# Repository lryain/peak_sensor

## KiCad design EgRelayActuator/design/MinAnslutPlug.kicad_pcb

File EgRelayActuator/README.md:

**CAUTION: This project deals with hazardous voltage with the risk of death or personal injury! Please don't do anything unless you are absolutely sure of what you are doing. There is no one liable for the correctness or usage of any information below.**

**Work In Progress**

Discussion, work and various projects have been done or are still going on regarding powering our MySensor/Arduino projects from mains supply. So I think the interest in these projects are pretty high. For this reason I decided to share this project as "work in progress" even though I prefer more completeness before publishing. The prototype PCB needs a couple of minor modifications to work. I only share Kicad design files without Gerbers to make sure anyone doesn't order it without being aware of the necessary mods.

**The Project Concept**

Yet another outlet switch? Well, yes, maybe. Hopefully you'll think I've added some value to it...

I think everyone have seen the cheap remote controlled wireless power outlet switches (here in Sweden usually at 433MHz). They're found in every store. Some are very simple with just a remote control and unknown protocol. Some are rather compatible and then makes quite good as e.g. entry level HA system or part of system. I think most DIY HA system controllers also have the ability to control those protocols and there's also sniffers, bridges and whatever necessary. Here are some threads I found just by a quick search here at the forum:

[http://forum.mysensors.org/topic/2286/experimenting-with-cheap-433mhz-gadgets](http://forum.mysensors.org/topic/2286/experimenting-with-cheap-433mhz-gadgets)

[http://forum.mysensors.org/topic/1621/mysensors-and-433-mhz](http://forum.mysensors.org/topic/1621/mysensors-and-433-mhz)

[http://forum.mysensors.org/topic/1543/universal-gateway-for-315-433mhz-devices](http://forum.mysensors.org/topic/1543/universal-gateway-for-315-433mhz-devices)

[http://forum.mysensors.org/topic/944/one-way-on-how-to-reuse-433mhz-alarming-sensors-for-mysensors](http://forum.mysensors.org/topic/944/one-way-on-how-to-reuse-433mhz-alarming-sensors-for-mysensors)

[http://forum.mysensors.org/topic/1557/combined-mysensor-gateway-with-433mhz-transmitter-homeeasy-klik-aan-klik-uit](http://forum.mysensors.org/topic/1557/combined-mysensor-gateway-with-433mhz-transmitter-homeeasy-klik-aan-klik-uit)
.

What I dislike most about these simple wireless switches are: (1) No duplx (ack) ability. (2) Unreliable reception. (3) They could interfere with each other if too close. (4) No Atmega328p - no playing.
(The more I think about it, the more important is the last (4).)

What I do like most: (1) Cheap (2) Good range. (3) Low power. (4). Small size. 

My first idea was to reuse as much as possible and MySensorize one of these common commercial wall-plugs. I did a few tries reusing some parts of the hardware (PCB and power supply) and squeeze in an Arduino Pro Mini and nRF24L01. I failed. The available power wasn't enough because of the relay and when I upgraded the transformerless supply it became to big to fit in the original enclosure. Thus, I looked for a switching transformer supply instead.

Transformerless supplies are great for low power [class II](http://www.ee-techs.com/test/en60335-1.pdf) devices like this since they're completely insulated. A transformer (-based switch mode-) supply is better for class III devices where the secondary voltage is touchable. But, in this case I had to go for transformer supply because of the space. I can see disadvantages with this choice; (1) Safety - It's much more complex and when ordering from China I'd prefer to trust a single X-cap rather than a whole power supply assembly. (2) Cost - (Not really, because it isn't as great difference as it used to be. Especially considering the work effort with more components of you build a transformerless supply from scratch.). 

To make it easy to design and useful for other future projects as well, I looked for a smaller switched mode power supply (SMPS) than [the famous HLK-PM01](http://lygte-info.dk/review/Power%20Mains%20to%205V%200.6A%20Hi-Link%20HLK-PM01%20UK.html) and then I had to do my own little review of it in [this thread.](http://forum.mysensors.org/topic/3428/my-look-at-a-cheap-12v-power-supply).

**The Enclosure and Original Product**

I went to a local shop and bought the cheapest 3-pack I could find, six months ago. I can't find it at that price (99SEK) any more, but the enclosure is (the most?) common, used by different brands and I guess very available in general. In worst case my new hardware of this project could be redesigned to fit other enclosures.

The internal parts of the original product is like every other of these: Xcap-rectifier-filter, relay, tiny uC with eeprom, radio circuit, etc. Note all the unused space inside the enclosure. Yum yum.

Since I don't have the right triangular shaped tool to release the two screws holding the case halves together, I replaced them as soon as I released them (with a normal flat headed screwdriver of the right size). I found that the screws included in the [10pcs Magnetic Door Switch Sensors](http://www.mysensors.org/store/#locks) make a perfect replacement for these.

**The New Hardware**

Here's my initial requirements. It's important to know that the objective of this first design was to (1) Be safe and (2) Collect info enough to assess reliability. It was not intended to be a final version.

- Standard 5x20mm glass fuse. Proven, high breaking capacity, replaceable and flexible (e.g. testing different values). 
- Thermal fuse(s). Protecting from supply and/or relay overheating consequences.
- Ability to measure temperatures of liable internal overheaters individually.
- Creepage distances with safety margin and a general HV-LV as well as HP-LP separation.
- Heat resistant assembly with robust withstanding insulation between HV conductive parts.
- Standard relay, minimum 10A rated.
- Low high-power resistance.
- EMC (hard to test though)
- Basic MySensors and Arduino functionality, FTDI, ISP
- No new enclosure penetrations (keep it class II)  

Running my Kicad, I came up with this:

Populated it looks like this:

and with lid on it looks like this. As can be seen, instead of one button and one LED, I've put three LEDs.

Features of this prototype fulfil my overall requirements listed above (...I think. I really need a second opinion though.) To be more specific:

- Robust assembly where the supply module is attached to main PCB by multiple solder points and then main PCB are screwed in place at original fixation points.
- 5x20mm fuse in semi-covered fuse holder.
- Thermal fuse guarding the supply controller temperature
- Varistor 10D391K
- 12V switch mode supply with voltage-, current-, temperature protections and manageable EMI. (The supply module is the YS-12V400-B which I studied closer [here](http://forum.mysensors.org/topic/3428/my-look-at-a-cheap-12v-power-supply))
- Songle 12V 10A relay
- Thermal fuse guarding the relay temperature 
- Thermistors to monitor supply and relay temperatures
- Divider to monitor internal voltage and detect blown relay termo-fuse.
- As good creepage distance as possible and reasonable with respect to the supply input footprint
- Low resistance solder-filled high-power traces
- Higher resistance trace to internal power supply
- FTDI pins (only accessible by opening the enclosure.)
- ISP port (needs removal of the nRF24L01+ away from its socket).
- One yellow LED for passive status indication of relay state
- One blue and one red LED controlled from uC
- nRF antenna positioned near top and front of device (unfortunately also near the switch supply trafo, but it doesn't seem to cause any problem)

Kicad design files are shared, but there are a few minor fixes needed because of a few embarrassingly stupid but small errors. Gerbers not included due to this. See further below for furture development plans.
Here's the board issues and necessary modifications:

- The +/- of the power module have been shifted. Solve by cutting traces and add jumper wires.
- The LED transistors (Q2 and Q3) have wrong footprint and must be placed 60' clockwise.
- The 5x20mm semi-closed fuse holder is placed 1-2mm too south and needs to be trimmed a little on the top edge to fit inside enclose. So put it with the lid hinge in the other end.
- The mounting hole in board middle is 0.5-1mm too small. The original screw fits, but not very nicely.
There're also some value adjustments needed:
- Fuse value (0.1A) is much too low. Instead I'd recommend a 0.3-0.5A fast fuse.
- The blue and yellow LEDs are a bit to bright. Increase R4 and R11 some to fix that.

A warning to all beginners: This project requires a lot of skilled soldering. There are size 0603 SMD parts mixed with bigger parts and if you don't follow a plan for assembling and then test it step-by-step as you build, you'll probably never get it to work in the end. I haven't written an exact build order, but of course small SMDs must be soldered early for practical reasons. I think a good order to build and test is something like:
 
1. SMDs
2. nRF socket (to program uC bootloader via ISP, don't forget the 9th (Reset) pin. I use the standard Arduino Pro Mini 8MHz bootloader.) 
3. Avr-FTDI (test with Arduino IDE serial monitor)
4. nRF
5. 12V
7. LEDs and thermistors
8. Relay and relay control parts
9. Thermal fuses (the one to the supply must soldered, before the glass fuse holder, to the board bottom side. Then folded up between supply module and board.)
10. 5x20 glass fuse holder and supply module (YS-12V400-B or HX-12V400)
11. Attach (solder) to the three line cables. (Double check to get it right.) 

The legs of the thermistors and the thermal fuse to the supply must be insulated. Find some suitable wire, strip it off and pull the insulation on to the new parts.

And of course: Never ever do anything with 230V connected! 
Use 12V battery for testing the low voltage sections and functions, and test the high voltage and supply sections separately. I like to use battery instead of 12V supply to avoid risk of ground loop when powering 3.3V through FTDI (from my laptop) at the same time. 

**The Sketch**

The sketch is aimed at testing and utilizes all the supported on-board hardware and tests LEDs, relay and status parameter conditions at start-up. Status conditions are monitored at start-up as well as during runtime. Errors and warnings are distinguished, processed and indicated through LED, coded controller messages and debug prints. Internal temperatures and voltage levels are measured every 1-3s (just my suggested set option) and reported at some optional interval to the controller. The error handling needs some improvement I think. E.g. there's sometimes a "low voltage error" when disconnecting the device from mains. Alarm (warning) and halt (error) levels need trimming and some hysteresis and "cooling-off delays".
I know there's a lot of repeated code, few comments and probably other horrible software practices. Please disregard. It was quickly done and coding isn't my favourite part of this cooking.
Thermistor calibration is done on a typical device, not every individual (e.g. this one). Accuracy seems to be good enough anyway, +/-3'C. (OT: If I some day automate my calibration process (off-line non-linear least mean square curve-fitting), it could be done for every node.)   

**Testing**

Start-up inrush current values are presented in [the supply review thread](http://forum.mysensors.org/topic/3428/my-look-at-a-cheap-12v-power-supply).

Current measurements at 239V AC:
The succeeding "load" inrush current peaks at 15-20mA(rms) for <1s (just by looking at my Fluke). Then a few seconds at 8mA to finally settle at 6.5mA. With pulled relay this is 13.5mA at startup and then settled at 11mA. 
It means 1.5W power consumption at stand-by and 2.6W when relay is on. Ok, I think. Still in the very low load region of [the supply load table](http://forum.mysensors.org/topic/3428/my-look-at-a-cheap-12v-power-supply)), which is good according to my EMI guesses/theories in that thread.

Load and Temperature:
To be able to shoot the thermal images it's necessary to run with open enclosure. In theory, all temperatures will be higher after time in a sealed enclosure. It's anyway good the see how much different parts heat up compared to each other, and during which conditions.

First image from one hour at idle. Highest temps measured to be the supply uC and rectifier diode and the AMS1117. All 35-38'C maximum. The supply uC heat isn't visible due the thermal fuse on top. Thermal fuses are not (yet) directly attached with thermal paste or glue, but it's on the to-do list. 

Next to the relay. A couple of minutes toggling the relay on-off at 0.5Hz with a 11A (at 239V) resistive load will look like this image below. Max temp ~40'C. It's easy to see that the heat is concentrated to the south part of the relay and that the thermal fuse is placed very good. I guess an inductive load would be much worse, but I haven't yet got to it.

Next two relay images show status after several minutes at a continuous 11A load. Max temp 55'C. This test generated much more heat than the toggle test. Also I think maybe the bottom image illustrates the importance of solder-reinforce the high power traces - there's a lot more heat where I scrimped with solder paste.

Here are the controller (Fhem) registrations from the temperature sensors during a test. Plug connected to outlet at 14:00, 11A load is switched on at 14:10 and switched off at 14:17.

**Future Development**

This project was a little more time consuming than I'd planned. There were few aspects to it and I really want to reassure myself that it was a feasible (safe) design. So it's still far from finished. But working. What I need to do next is:

- Clear the board issues above.
- Attach thermal fuses with thermal paste or glue.
- Max inductive load endurance test.
- Build a few more prototypes.
- Install in "safe places" and set proper controller alarm and measures (back-up switch?).
- More operation time and collect more statistics.

**Version 2.0**

Along with this board version 1.0 I've also designed a 2.0. Is intended to be more of a production version rather than for testing. It has: 

- One DS18B20 instead of thermistors (thermal fuses are kept of course)
- ATSHA204 (for signing purpose)
- External flash (for dual FTDI and OTA bootloader)

Unfortunately I got stuck quite early at the testing with the 2.0 prototype version. And I don't know when I'll have time to pick it up. If anyone is interested I think it's better to share that design in a separate thread and develop as a fork to the progress of this "test" version 1.0.

That's it. Unfortunately I can't estimate any schedule for finish this project, but I've had great fun wiith it so far. Hope you'll enjoy too.

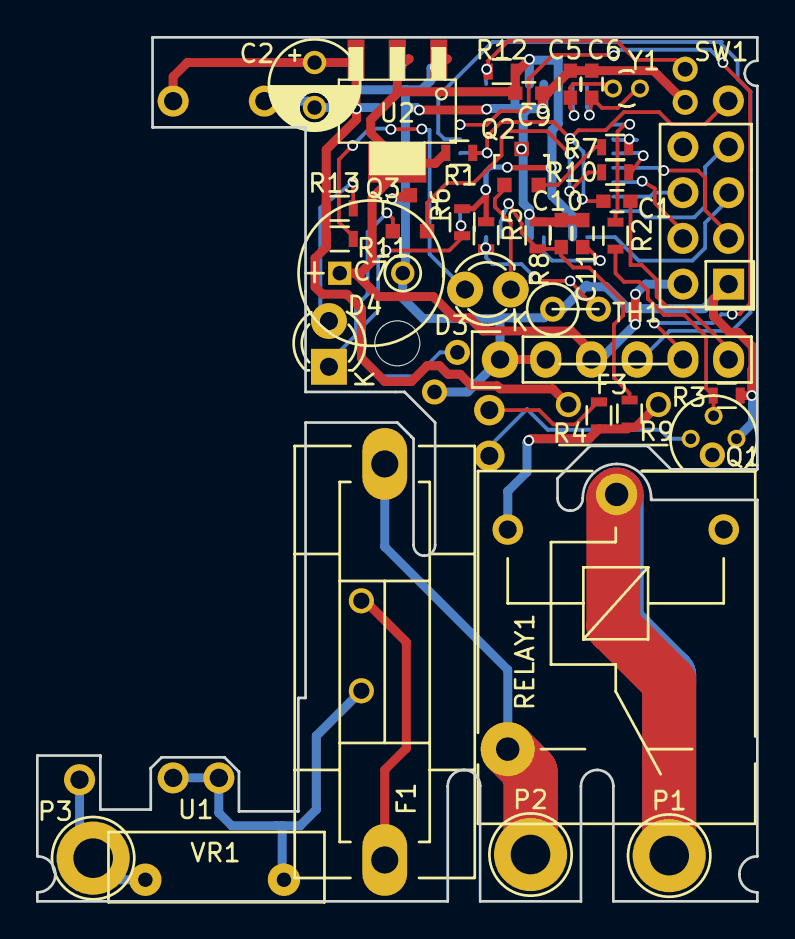
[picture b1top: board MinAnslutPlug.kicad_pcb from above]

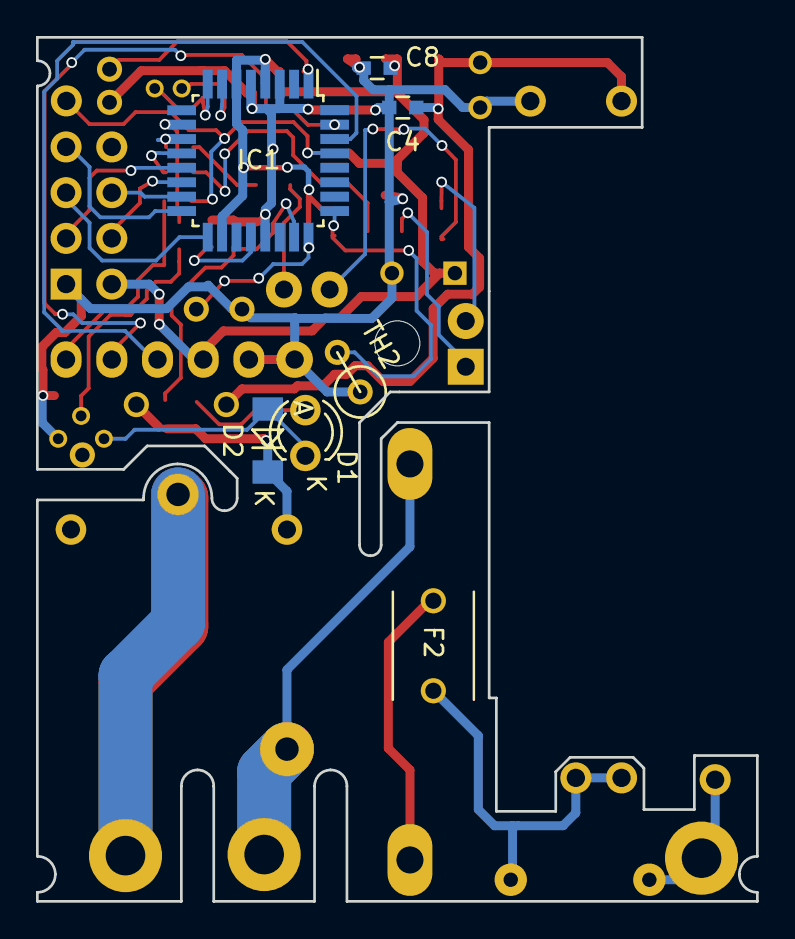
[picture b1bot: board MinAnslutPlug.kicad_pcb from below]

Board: 2 copper layers, 40.0 x 48.0 mm, 50 parts (7 on the bottom side), 37 nets.

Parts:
C1, C5, C6, C8, C9, C10, C11: C_0603
C2: C_Radial_D5_L6_P2.5
C4: 0.1uF; C_0603
C7: C_Radial_D8_L11.5_P3.5
D1, D3: LED; LED-3MM
D2: MiniMELF_Standard
D4: LED-3MM
F1: 0.1A; Fuseholder5x20_horiz_SemiClosed_Casing10x25mm
F2, F3: C_Disc_D6_P5
H1: MountingHole_2-5mm
IC1: TQFP-32_7x7mm_Pitch0.8mm
JMP1: WireConnection_0.80mmDrill_ThinPad
P1: AC_out; 1pin
P2, P3: AC_in; 1pin
P4: Pin_Header_Straight_1x06
P6: NRF24L01
P7: Socket_Strip_Straight_1x01
Q1: TO-92_Molded_Narrow
Q2, Q3: SOT-23
R1, R2, R3, R4, R5, R6, R7, R8, R9, R10, R11, R12, R13: R_0603
RELAY1: Relay_SANYOU_SRD_Series_Form_C
SW1: Pin_Header_Straight_1x02
TH1, TH2: R1
U1: HX-12V400X; YS-12V400-B
U2: AB2_SOT223
VR1: VR; RV_Disc_D12_W3.9_P7.5
Y1: Crystal_Round_Vertical_2mm

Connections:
+12V: C2.1, C4.1, F3.1, R11.1, R13.1, U1.3, U2.3
/12V_relay: D2.1, F3.2, R4.1, R9.1, RELAY1.4
/A0: C10.1, IC1.23, R8.2, R9.2
/A1: IC1.24, R5.2, TH1.2
/A2: IC1.25, R6.2, TH2.2
/D3: IC1.1, R12.2, SW1.2
/D6: IC1.10, R2.1
/D7: IC1.11, R7.2
/D8: IC1.12, R10.2
/D9(CE): IC1.13, P6.3
/D10(SS): IC1.14, P6.4
/D11(MOSI): IC1.15, P6.6
/D12(MISO): IC1.16, P6.7
/D13(SCK): IC1.17, P6.5
/DTR: C1.1, P4.6
/RESET: C1.2, IC1.29, P7.1, R1.2
/RX: IC1.30, P4.4
/TX: IC1.31, P4.5
/X1: C5.2, IC1.7, Y1.1
/X2: C6.2, IC1.8, Y1.2
GND: C2.2, C4.2, C5.1, C6.1, C7.2, C8.2, C9.2, C10.2, C11.2, IC1.3, IC1.5, IC1.21, P4.1, P4.2, P6.1, Q1.3, Q2.3, Q3.3, R3.1, R8.1, SW1.1, TH1.1, TH2.1, U1.4, U2.1
unnamed: C11.1, IC1.20
unnamed: D1.1, D2.2, Q1.1, RELAY1.5
unnamed: D1.2, R4.2
unnamed: D3.1, Q2.1
unnamed: D3.2, R11.2
unnamed: D4.1, Q3.1
unnamed: D4.2, R13.2
unnamed: F1.1, P2.1, RELAY1.1
unnamed: F1.2, F2.2
unnamed: F2.1, U1.2, VR1.1
unnamed: P1.1, RELAY1.3
unnamed: P3.1, U1.1, VR1.2
unnamed: Q1.2, R2.2, R3.2
unnamed: Q2.2, R7.1
unnamed: Q3.2, R10.1
VCC: C7.1, C8.1, C9.1, IC1.4, IC1.6, IC1.18, P4.3, P6.2, R1.1, R5.1, R6.1, R12.1, U2.2

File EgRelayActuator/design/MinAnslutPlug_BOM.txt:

Count	Reference	Value	Footprint
6	C1 C4 C8 C9 C10 C11	0.1uF	Capacitors_SMD:C_0603																		
1	C2	4.7uF	Capacitors_ThroughHole:C_Radial_D5_L6_P2.5																		
2	C5 C6	22pF	Capacitors_SMD:C_0603																		
1	C7	100uF	Capacitors_ThroughHole:C_Radial_D8_L11.5_P3.5																		
1	D2	1N4148	Diodes_SMD:MiniMELF_Standard																		
3	D1 D3 D4	LED	LEDs:LED-3MM																		
1	F1	0.1A	Fuseholder5x20_horiz_SemiClosed_Casing10x25mm																		
2	F2 F3	FUSE	Capacitors_ThroughHole:C_Disc_D6_P5																		
1	IC1	ATMEGA328P-A	Housings_QFP:TQFP-32_7x7mm_Pitch0.8mm																		
1	P1	AC_out	Connect:1pin																		
2	P2 P3	AC_in	Connect:1pin																		
1	P4	Arduino Serial	Pin_Headers:Pin_Header_Straight_1x06																		
1	P6	NRF24L01+	mysensors_radios:NRF24L01																		
1	P7	ICSP RESET	Socket_Strips:Socket_Strip_Straight_1x01																		
1	Q1	BC517	TO_SOT_Packages_THT:TO-92_Molded_Narrow																		
2	Q2 Q3	BC546	TO_SOT_Packages_SMD:SOT-23																		
2	R1 R2	10k	Resistors_SMD:R_0603																		
1	R11	680	Resistors_SMD:R_0603																		
2	R4 R13	1k	Resistors_SMD:R_0603																		
4	R3 R5 R6 R12	100k	Resistors_SMD:R_0603																		
2	R7 R10	47k	Resistors_SMD:R_0603																		
1	R8	470k	Resistors_SMD:R_0603																		
1	R9	10M	Resistors_SMD:R_0603																		
1	RELAY1	SONGLE_RELAY	Relay_SANYOU_SRD_Series_Form_C																		
1	SW1	SW_PUSH	Pin_Headers:Pin_Header_Straight_1x02																		
2	TH1 TH2	THERMISTOR	Discret:R1																		
1	U1	HX-12V400X	Pin_Headers:Pin_Header_Angled_2x02																		
1	U2	AMS1117	ab2_sot:AB2_SOT223																		
1	VR1	VR	Varistors:RV_Disc_D12_W3.9_P7.5																		
1	Y1	8MHz	Crystals:Crystal_Round_Vertical_2mm

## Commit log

2016-12-18 refactory
2017-01-20 datasheet
